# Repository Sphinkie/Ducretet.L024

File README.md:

# Ducretet.L024
 Vintage MP3 player

### Credits

https://www.pistonsoft.com/bpm-detector.html

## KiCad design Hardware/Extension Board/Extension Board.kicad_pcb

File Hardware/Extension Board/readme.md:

# DUCRETET L.024

## Extension Board

### Principe

Cette carte réalise l'adaptation des différents controles avec les Entrées/Sorties de l'Arduino.

### Fonctionnalités

* Adaptation pour les LEDs
* Adaptation pour les lampes
* Adaptation pour la lecture du condensateur variable
* Adaptation pour lecture du Mode
* Adaptation pour lecture du commutateur Next/Again
* Etage alimentation : 6V / 12V

### Connexions

* **CNX MODE** = 4 pins : GND + Mode1 + Mode2 + Mode3
* **CNX OLED** = 4 pins = VCC + GND + SDA + SCL (bus I2C)
* **CNX NEXT_AGAIN** = 3 pins = GND + Next + Again
* **CNX LEDS** = 5x 2 pins = VCC + LED_n
* **TEST POINTS** = Vin + 6V + 12V + GND
* **JMP_TUNE** = 2 jumpers : Use_C1 + Use_C2
* **CNX TUNE** = 3 pins = C0 + C1 + C2

### Etage Alimentation

* **CNX_LAMPS** = 2 pins = 6V + LAMPS
* **CNX6V ** = 2 pins = VCC + GND  = Wire2board vers Arduino
* **CNX 12V** = 2 pins = 12V + GND  = Wire2board vers Ampli
* **CNX POWER_IN** = 2 pins = VIN + GND  = Wire2board
* **CNX ON_OFF** = 2 pins

## Schemas

Le **schema électronique** est accessible ici: [Extension board schematic](Extension%20Board.pdf).

ainsi que  le schéma d'implantation (couche de fabrication) [Extension Board PCB](Gerbers/Extension%20Board-F_Fab.pdf).

et le schéma du PCB [Extension Board PCB](Extension%20Board%20PCB.pdf).

Accès à la [Bill Of Material](https://sphinkie.github.io/Ducretet.L024/BOM-ExtensionBoard.html).

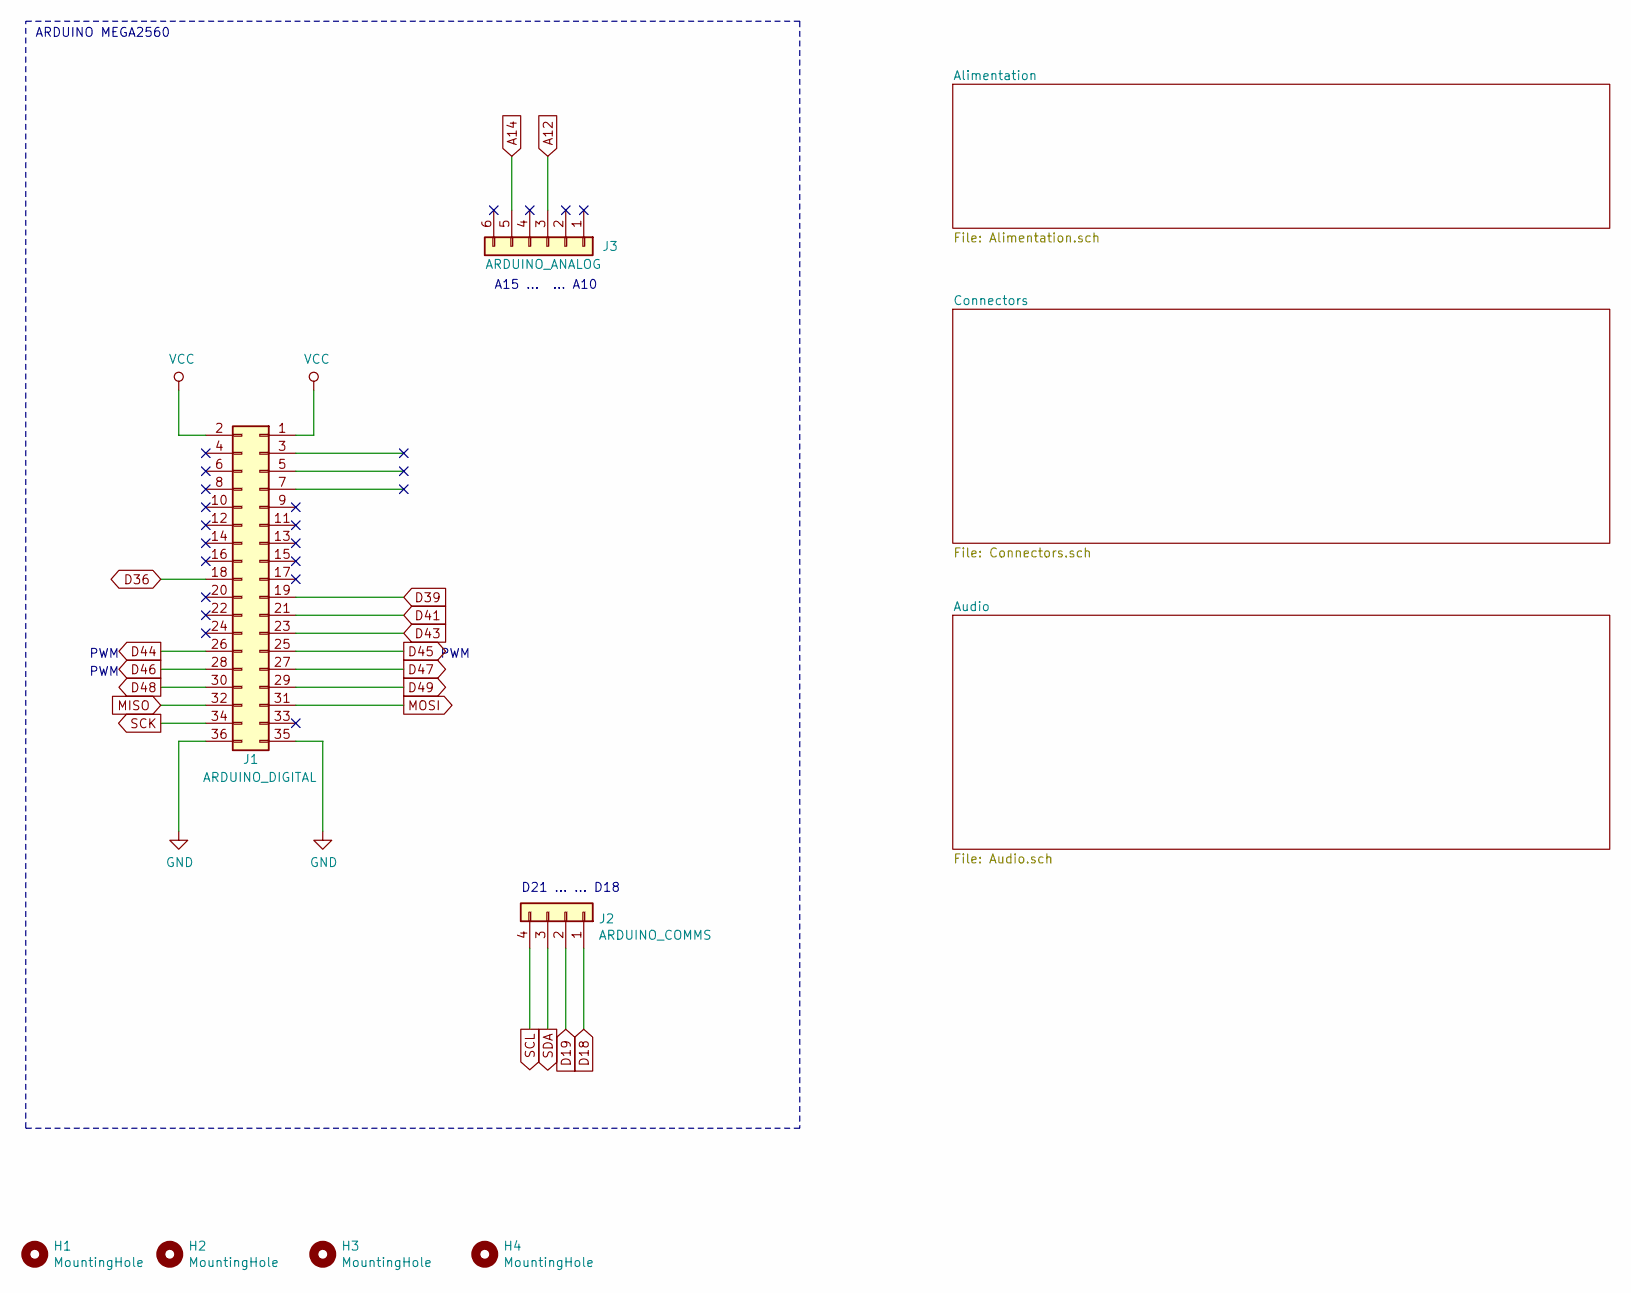
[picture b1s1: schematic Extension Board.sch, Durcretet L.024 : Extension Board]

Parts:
H1, H2, H3, H4: MountingHole; MountingHole_2.7mm_M2.5
J1: ARDUINO_DIGITAL; PinHeader_2x18_P2.54mm_Vertical
J2: ARDUINO_COMMS; PinHeader_1x04_P2.54mm_Vertical
J3: ARDUINO_ANALOG; PinHeader_1x06_P2.54mm_Vertical

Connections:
A12: J3.3; also elsewhere on the board
A14: J3.5; also elsewhere on the board
D18: J2.1; also elsewhere on the board
D19: J2.2; also elsewhere on the board
D36: J1.18; also elsewhere on the board
D39: J1.19; also elsewhere on the board
D41: J1.21; also elsewhere on the board
D43: J1.23; also elsewhere on the board
D44: J1.26; also elsewhere on the board
D45: J1.25; also elsewhere on the board
D46: J1.28; also elsewhere on the board
D47: J1.27; also elsewhere on the board
D48: J1.30; also elsewhere on the board
D49: J1.29; also elsewhere on the board
GND: J1.35, J1.36; also elsewhere on the board
MISO: J1.32; also elsewhere on the board
MOSI: J1.31; also elsewhere on the board
SCK: J1.34; also elsewhere on the board
SCL: J2.4; also elsewhere on the board
SDA: J2.3; also elsewhere on the board
VCC: J1.1, J1.2; also elsewhere on the board

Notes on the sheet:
ARDUINO MEGA2560
A15 ... ... A10
D21 ... ... D18
PWM
PWM

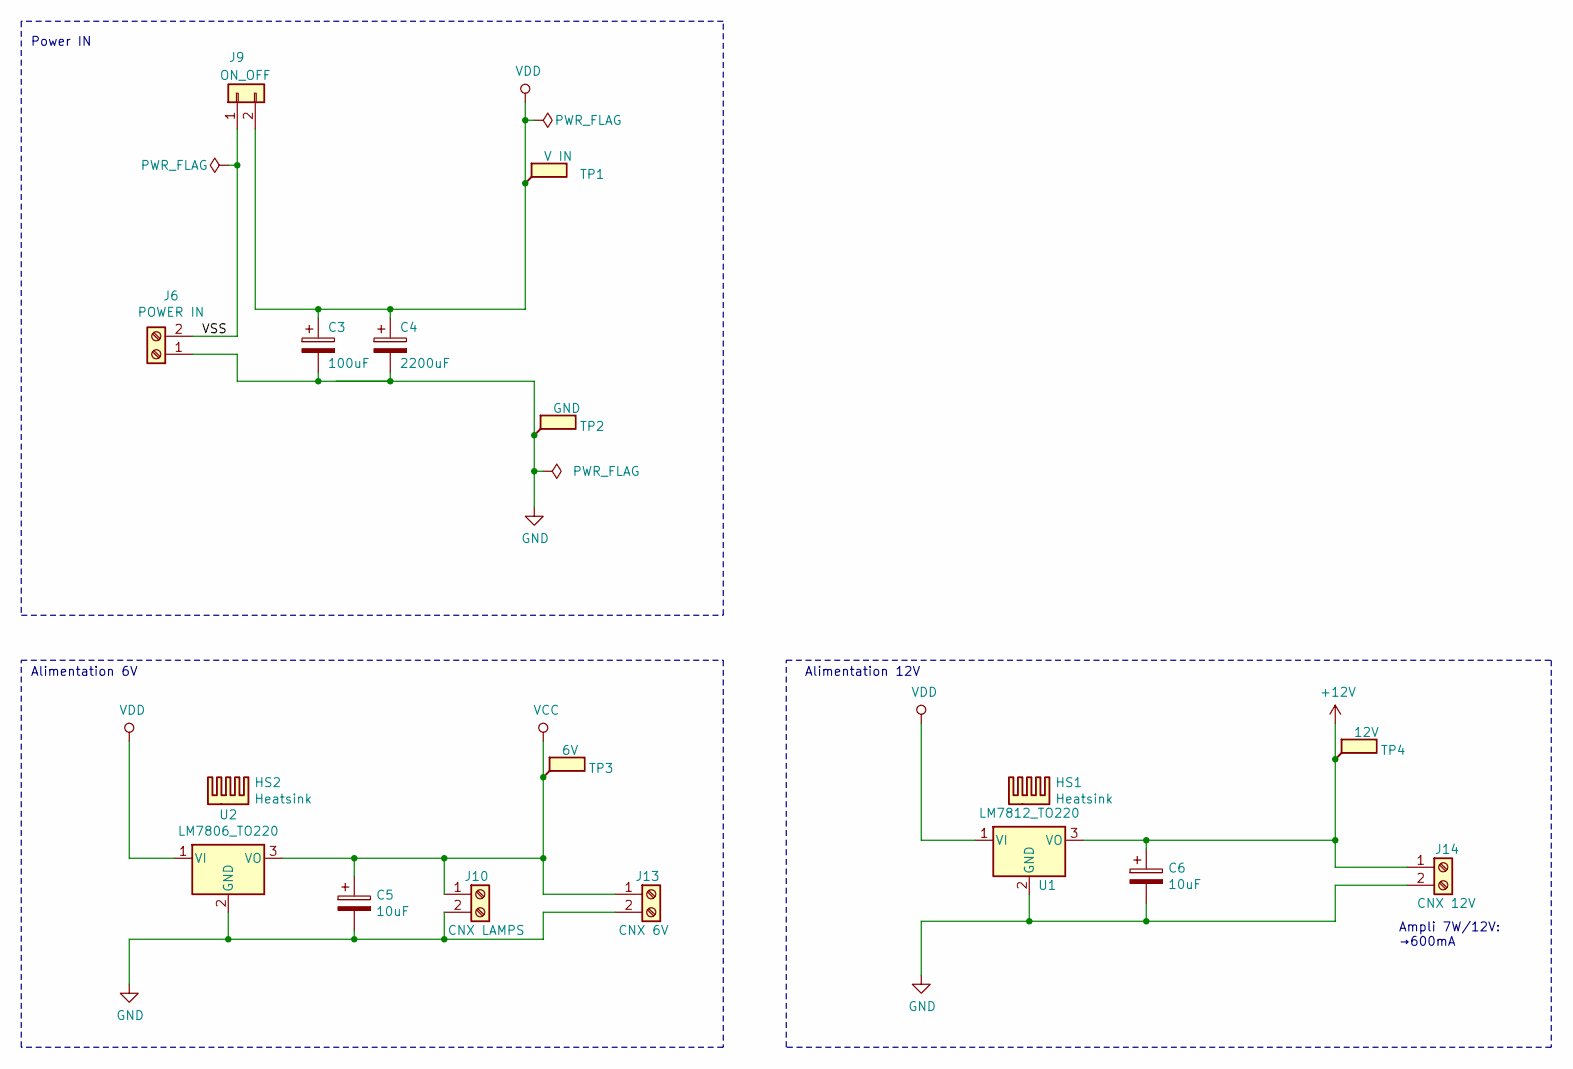
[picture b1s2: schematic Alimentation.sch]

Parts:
C3: 100uF; CP_Axial_L18.0mm_D8.0mm_P25.00mm_Horizontal
C4: 2200uF; CP_Axial_L30.0mm_D18.0mm_P35.00mm_Horizontal
C5, C6: 10uF; CP_Radial_D5.0mm_P2.50mm
HS1, HS2: Heatsink; HeatSink_TO-220
J6: POWER IN; TerminalBlock_Phoenix_MKDS-1,5-2-5.08_1x02_P5.08mm_Horizont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
J9: ON_OFF; JST_XH_B2B-XH-A_1x02_P2.50mm_Vertical
J10: CNX LAMPS; Bloc_de_jonction_CI-MPT_2.54mm_01x02
J13: CNX 6V; TerminalBlock_Phoenix_MKDS-1,5-2-5.08_1x02_P5.08mm_Horizont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
J14: CNX 12V; TerminalBlock_MetzConnect_Type011_RT05502HBWC_1x02_P5.00mm_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
TP1: V IN; TestPoint_Loop_D2.60mm_Drill1.4mm_Beaded
TP2: GND; TestPoint_Loop_D2.60mm_Drill1.4mm_Beaded
TP3: 6V; TestPoint_Loop_D2.60mm_Drill1.4mm_Beaded
TP4: 12V; TestPoint_Loop_D2.60mm_Drill1.4mm_Beaded
U1: LM7812_TO220; TO-220-3_Vertical
U2: LM7806_TO220; TO-220-3_Vertical

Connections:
+12V: C6.1, J14.1, TP4.1, U1.3 (VO)
/Alimentation/VSS: J6.2, J9.1
GND: C3.2, C4.2, C5.2, C6.2, J6.1, J10.2, J13.2, J14.2, TP2.1, U1.2 (GND), U2.2 (GND); also elsewhere on the board
VCC: C5.1, J10.1, J13.1, TP3.1, U2.3 (VO); also elsewhere on the board
VDD: C3.1, C4.1, J9.2, TP1.1, U1.1 (VI), U2.1 (VI)

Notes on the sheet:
Ampli 7W/12V: →600mA
Alimentation 12V
Alimentation 6V
Power IN

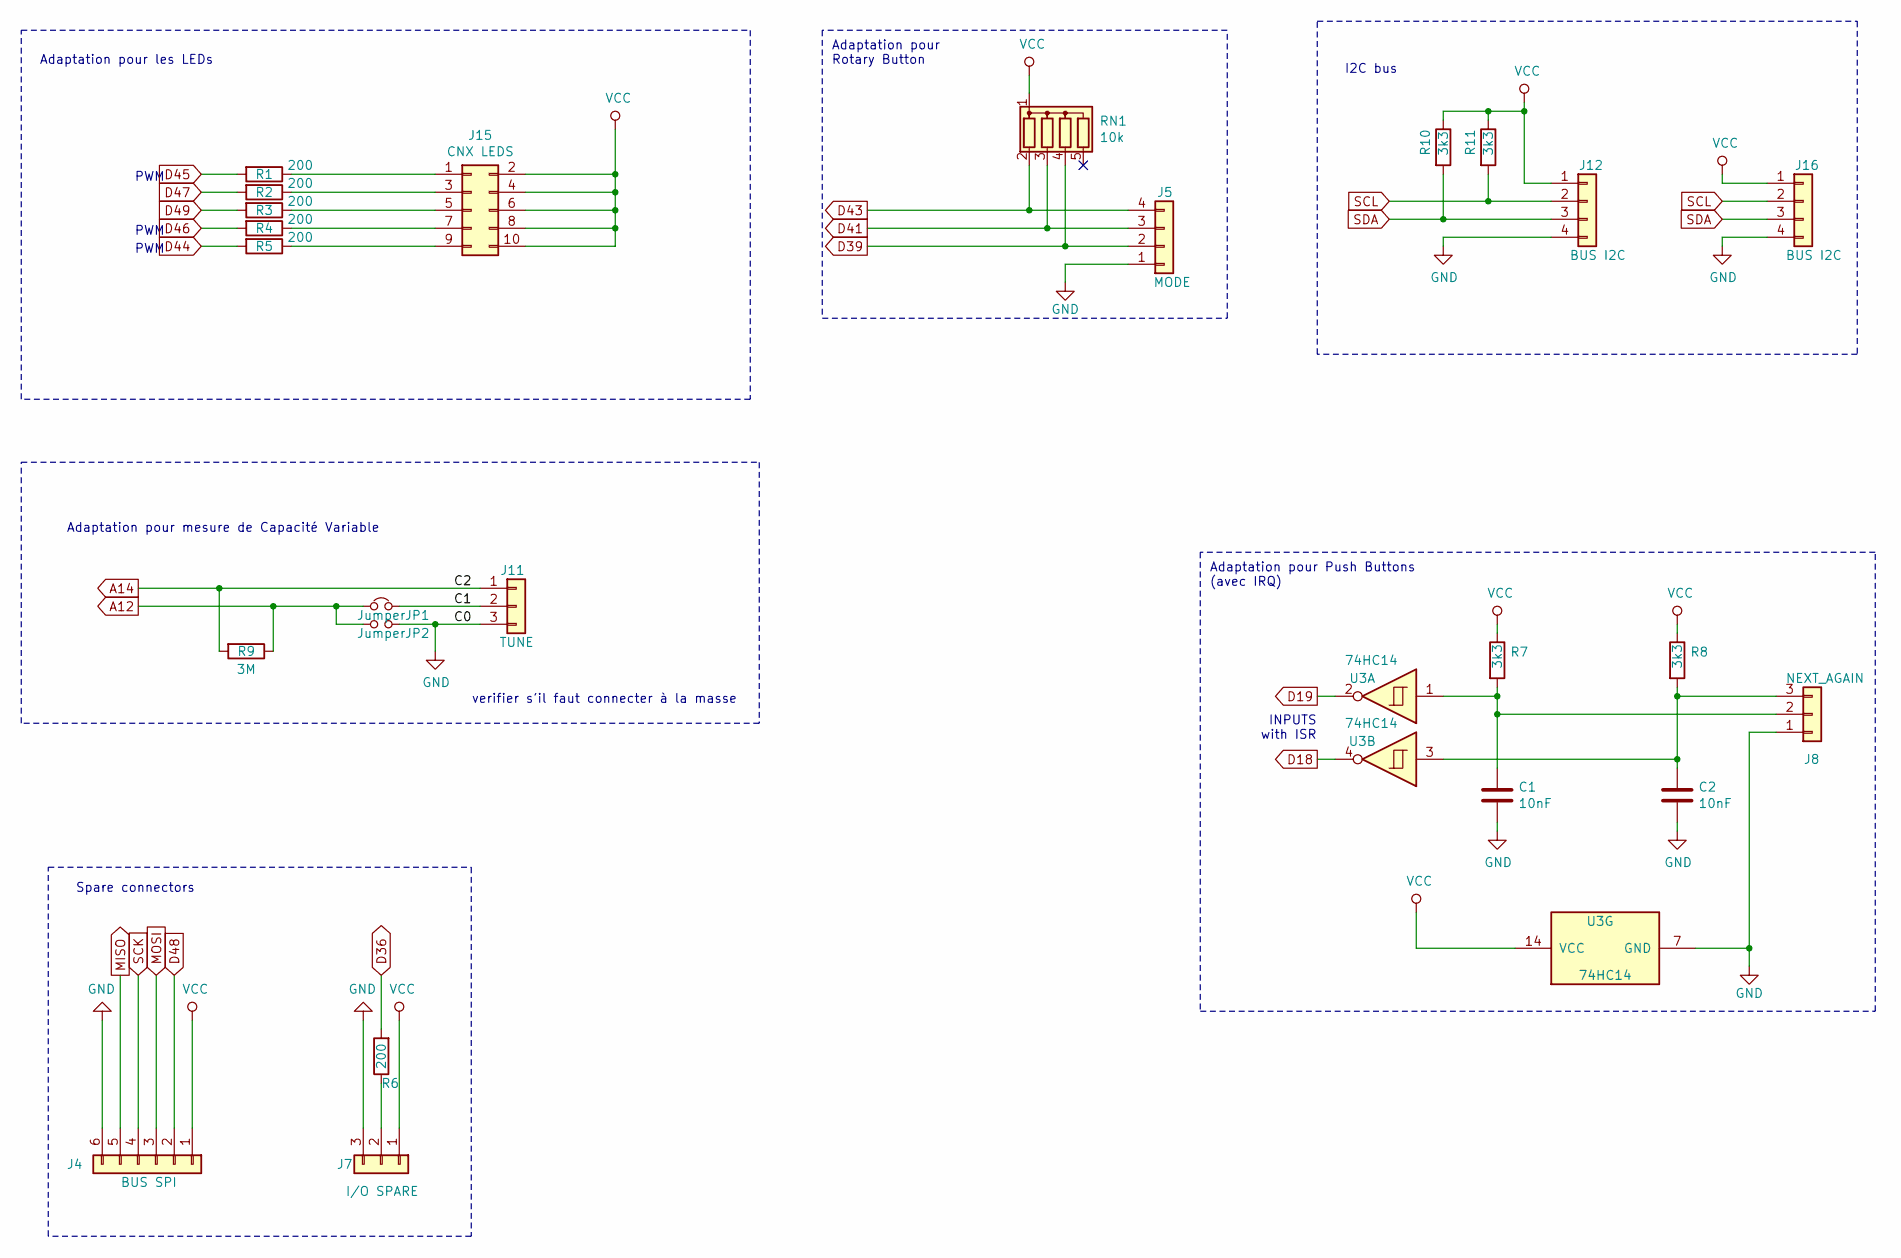
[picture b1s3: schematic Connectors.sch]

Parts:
C1, C2: 10nF; C_Rect_L7.2mm_W2.5mm_P5.00mm_FKS2_FKP2_MKS2_MKP2
J4: BUS SPI; JST_XH_B6B-XH-AM_1x06_P2.50mm_Vertical
J5: MODE; JST_XH_B4B-XH-A_1x04_P2.50mm_Vertical
J7: I/O SPARE; JST_XH_B3B-XH-AM_1x03_P2.50mm_Vertical
J8: NEXT_AGAIN; JST_XH_B3B-XH-A_1x03_P2.50mm_Vertical
J11: TUNE; JST_XH_B3B-XH-A_1x03_P2.50mm_Vertical
J12, J16: BUS I2C; JST_XH_B4B-XH-A_1x04_P2.50mm_Vertical
J15: CNX LEDS; HE10-10P-horizontal
JP1, JP2: Jumper; PinHeader_1x02_P2.54mm_Vertical
R1, R2, R3, R4, R5, R6: 200; R_Axial_DIN0207_L6.3mm_D2.5mm_P10.16mm_Horizontal
R7, R8, R10, R11: 3k3; R_Axial_DIN0207_L6.3mm_D2.5mm_P10.16mm_Horizontal
R9: 3M; R_Axial_DIN0309_L9.0mm_D3.2mm_P15.24mm_Horizontal
RN1: 10k; R_Array_SIP5
U3: 74HC14; DIP-14_W7.62mm_Socket_LongPads

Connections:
/Connectors/C1: J11.2, JP1.2
A12: JP1.1, JP2.1, R9.1; also elsewhere on the board
A14: J11.1, R9.2; also elsewhere on the board
D18: U3.4; also elsewhere on the board
D19: U3.2; also elsewhere on the board
D36: R6.2; also elsewhere on the board
D39: J5.2, RN1.4 (R3); also elsewhere on the board
D41: J5.3, RN1.3 (R2); also elsewhere on the board
D43: J5.4, RN1.2 (R1); also elsewhere on the board
D44: R5.2; also elsewhere on the board
D45: R1.2; also elsewhere on the board
D46: R4.2; also elsewhere on the board
D47: R2.2; also elsewhere on the board
D48: J4.2; also elsewhere on the board
D49: R3.2; also elsewhere on the board
GND: C1.2, C2.2, J4.6, J5.1, J7.3, J8.1, J11.3, J12.4, J16.4, JP2.2, U3.7 (GND); also elsewhere on the board
MISO: J4.5; also elsewhere on the board
MOSI: J4.3; also elsewhere on the board
unnamed: C1.1, J8.2, R7.2, U3.1
unnamed: C2.1, J8.3, R8.2, U3.3
unnamed: J7.2, R6.1
unnamed: J15.1, R1.1
unnamed: J15.3, R2.1
unnamed: J15.5, R3.1
unnamed: J15.7, R4.1
unnamed: J15.9, R5.1
SCK: J4.4; also elsewhere on the board
SCL: J12.2, J16.2, R11.2; also elsewhere on the board
SDA: J12.3, J16.3, R10.2; also elsewhere on the board
VCC: J4.1, J7.1, J12.1, J15.2, J15.4, J15.6, J15.8, J15.10, J16.1, R7.1, R8.1, R10.1, R11.1, RN1.1 (common), U3.14 (VCC); also elsewhere on the board

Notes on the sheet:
Adaptation pour les LEDs
PWM
Spare connectors
Adaptation pour Rotary Button
Adaptation pour Push Buttons (avec IRQ)
INPUTS with ISR
I2C bus
Adaptation pour mesure de Capacité Variable
verifier s'il faut connecter à la masse

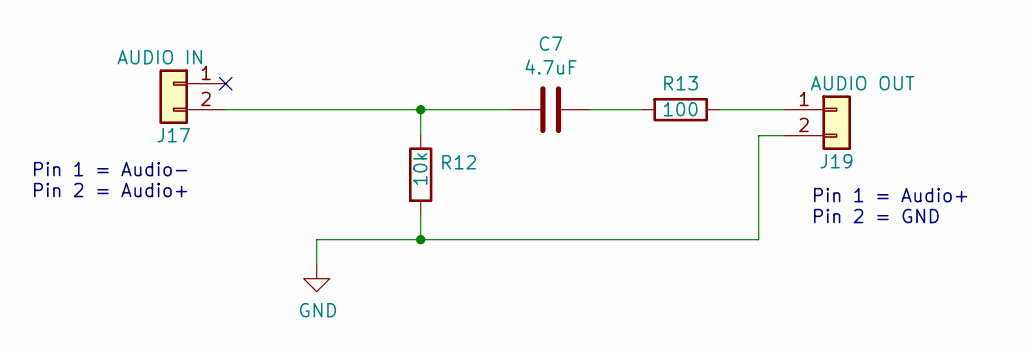
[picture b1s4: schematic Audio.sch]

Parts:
C7: 4.7uF; C_Axial_L17.0mm_D7.0mm_P25.00mm_Horizontal
J17: AUDIO IN; Bloc_de_jonction_CI-MPT_2.54mm_01x02
J19: AUDIO OUT; Bloc_de_jonction_CI-MPT_2.54mm_01x02
R12: 10k; R_Axial_DIN0207_L6.3mm_D2.5mm_P10.16mm_Horizontal
R13: 100; R_Axial_DIN0207_L6.3mm_D2.5mm_P10.16mm_Horizontal

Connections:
GND: J19.2, R12.2; also elsewhere on the board
unnamed: C7.1, J17.2, R12.1
unnamed: C7.2, R13.2
unnamed: J19.1, R13.1

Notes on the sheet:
Pin 1 = Audio- Pin 2 = Audio+
Pin 1 = Audio+ Pin 2 = GND

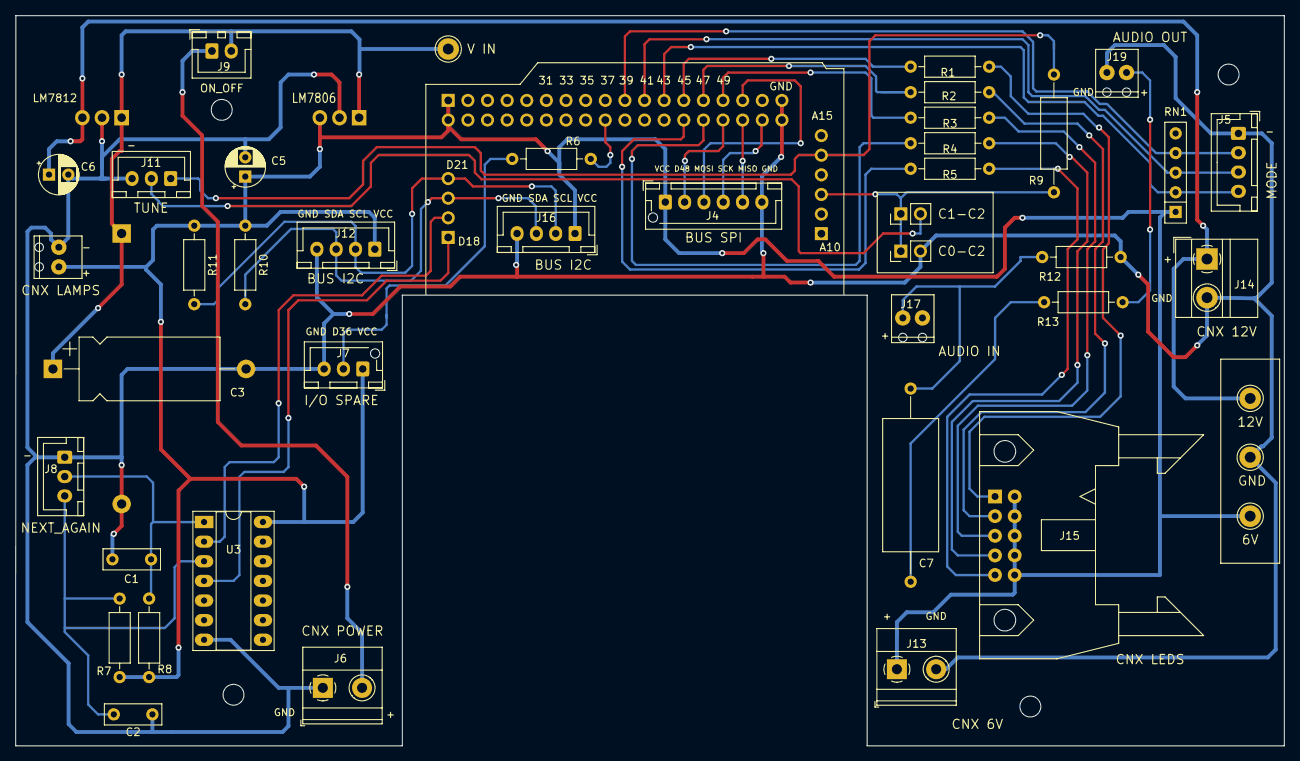
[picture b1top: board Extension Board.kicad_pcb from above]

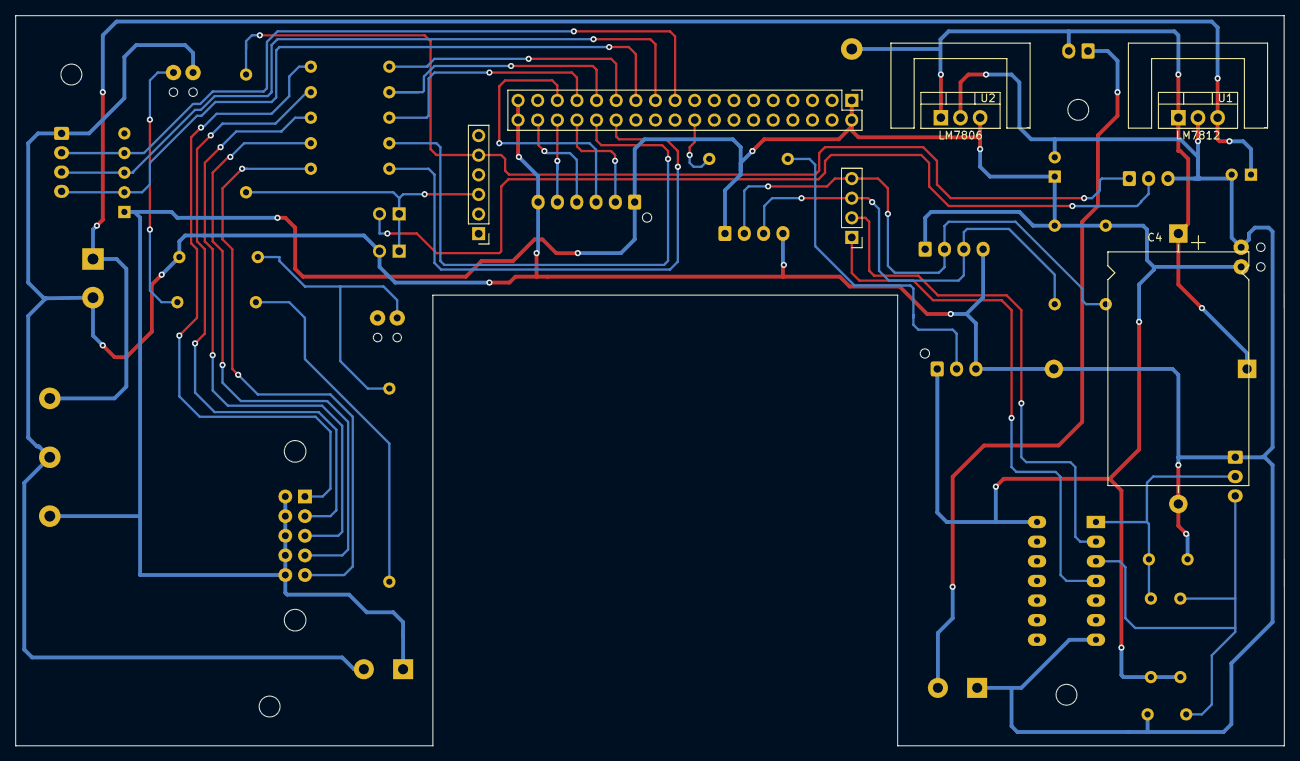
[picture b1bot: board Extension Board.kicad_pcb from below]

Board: 2 copper layers, 164.2 x 94.5 mm, 54 parts (8 on the bottom side), 36 nets.

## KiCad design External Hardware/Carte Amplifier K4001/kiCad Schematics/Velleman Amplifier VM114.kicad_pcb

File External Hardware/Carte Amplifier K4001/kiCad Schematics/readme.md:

# Ducretet L.024

## Amplifier Board : Schematics

Amplificateur audio mono 4W.

Ce répertoire contient le schéma électronique de la carte (au format KiCad).

[Vue du schéma électronique](Velleman%20Amplifier%20VM114.sch)

* Fichier **pro** : fichier **projet** Kicad
* Fichier **sch** : Schéma électronique Kicad
* Fichier **kicad_pcb** : fichier **PCB** Kicad

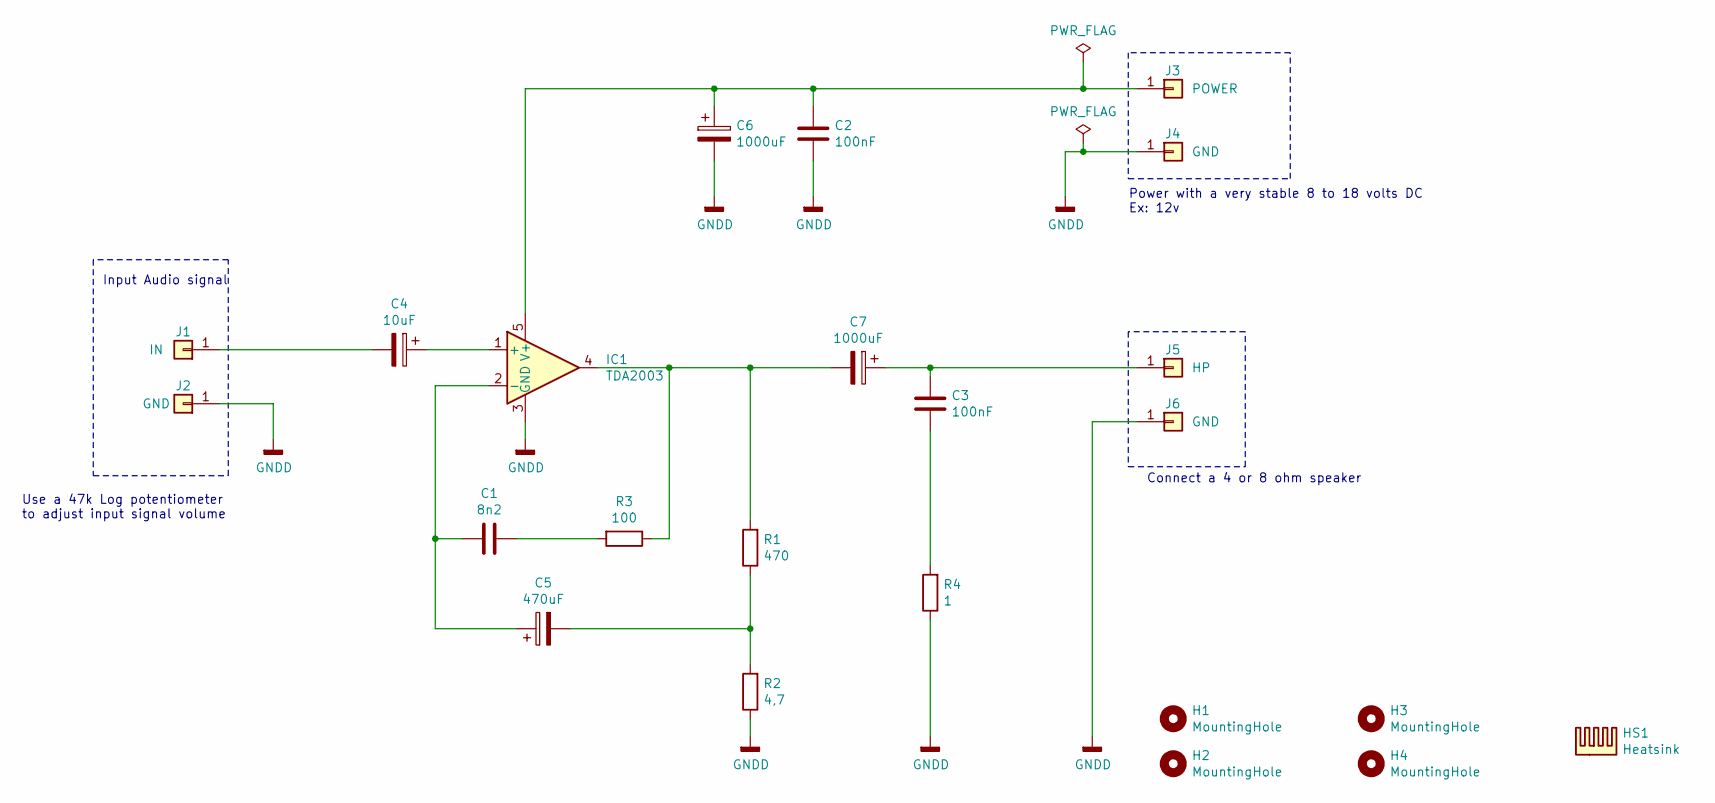
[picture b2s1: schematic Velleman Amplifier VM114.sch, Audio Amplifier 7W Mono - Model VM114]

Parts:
C1: 8n2; C_Disc_D4.3mm_W1.9mm_P5.00mm
C2, C3: 100nF; C_Disc_D4.3mm_W1.9mm_P5.00mm
C4: 10uF; C_Radial_D5.0mm_H11.0mm_P2.00mm
C5: 470uF; C_Radial_D6.3mm_H11.0mm_P2.50mm
C6, C7: 1000uF; C_Radial_D10.0mm_H20.0mm_P5.00mm
H1, H2, H3, H4: MountingHole; MountingHole_3.2mm_M3_DIN965_Pad
HS1: Heatsink; Heatsink_Stonecold_HS-132_32x14mm_2xFixation1.5mm
IC1: TDA2003; TO-220-5_P3.4x3.7mm_StaggerOdd_Lead3.8mm_Vertical
J1: IN; Pin_D1.0mm_L10.0mm
J2, J4, J6: GND; Pin_D1.0mm_L10.0mm
J3: POWER; Pin_D1.0mm_L10.0mm
J5: HP; Pin_D1.0mm_L10.0mm
R1: 470; R_Axial_DIN0204_L3.6mm_D1.6mm_P5.08mm_Horizontal
R2: 4,7; R_Axial_DIN0204_L3.6mm_D1.6mm_P5.08mm_Horizontal
R3: 100; R_Axial_DIN0204_L3.6mm_D1.6mm_P5.08mm_Horizontal
R4: 1; R_Axial_DIN0204_L3.6mm_D1.6mm_P5.08mm_Horizontal

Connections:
GNDD: C2.2, C6.2, IC1.3 (GND), J2.1, J4.1, J6.1, R2.1, R4.1
unnamed: C1.1, R3.2
unnamed: C1.2, C5.1, IC1.2 (-)
unnamed: C2.1, C6.1, IC1.5 (V+), J3.1
unnamed: C3.1, R4.2
unnamed: C3.2, C7.1, J5.1
unnamed: C4.1, IC1.1 (+)
unnamed: C4.2, J1.1
unnamed: C5.2, R1.1, R2.2
unnamed: C7.2, IC1.4, R1.2, R3.1

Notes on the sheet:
Input Audio signal
Connect a 4 or 8 ohm speaker
Power with a very stable 8 to 18 volts DC Ex: 12v
Use a 47k Log potentiometer to adjust input signal volume

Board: 2 copper layers, 23 parts (0 on the bottom side), 10 nets, no tracks yet.

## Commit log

2020-05-19 VERSION 0.1
2020-05-19 version compilable (avec bouchons)
2020-05-20 Ajout de la librarie Adafruit
2020-05-22 Lecture des tags MP3
2020-05-22 On remplace SDFAT.h par SD.h
    Pour ne pas avoir de conflit avec la librairie Adafruit qui utilise SD.h...
2020-05-22 test de 3 méthodes différentes pour récupérer les tags MP3
2020-05-25 Fusion de AddStar et RemoveStar
2020-05-25 Preparation de la carte SD
2020-05-25 Gestion du Field5 : le tag BPM
2020-05-26 Branchement Adafruit
2020-05-27 Reading ID3 tags in MP3 file
2020-05-27 WIP - playing MP3 file
2020-05-28 Fixed. Music is playing.
    Reading MP3 : disabled
2020-05-28 Read IDtags prend un parametre "File"
2020-05-30 v0.3 Mode Random OK.
2020-05-31 Mode YEAR + Mode GENRE
2020-05-31 WIP : Gestion des Beat
2020-05-31 Fix: rewind at ebd of decade.
2020-06-01 Fix: pb de ReadStringUntil() quand on arrive à EOF
    il faut tester: File.available()
2020-06-01 On ne garde le FirstMedia que pour la recherche par YEAR
2020-06-01 Fix: Recherche par YEAR.
2020-06-01 Recherche par BEAT = ok
2020-06-01 Adding ePaper Waveshare library
2020-06-02 Applications de test d'affichage sur ePaper
2020-06-08 ePaper display is replaced by I2C OLED display
2020-06-08 PCB pour Extension board
2020-06-09 PCB Extension board
2020-06-10 PCB Layout complete
2020-06-10 PCB updated.
2020-06-12 Classe Rythlmic opur la gestion du tempo
2020-06-12 gestion Beat
2020-06-15 Sample pictures
2020-06-16 Tests sur OLED display
2020-06-18 Gestion du scrolling pour les polices à taille fixe
2020-06-18 Gestion eds caractères accentués
2020-06-18 Implémentation OLED dans le projet
2020-08-01 update poru Github-Linguist
2020-08-01 update pour Github-Linguist
2022-03-09 Affichage des infos média
2022-03-10 Affichages
2022-03-12 Animation du titre
2022-03-18 Splash Screen
2022-03-20 Carte Ampli Audio
2022-03-20 Audio Amplifier documentation
2022-03-20 OLED Screen update
2022-03-21 Ajout de la documentation doxygen
2022-03-22 update doxyfile documentation
2022-03-31 update shematics
2022-04-03 Ajout FootPrint Library MesModules
2022-04-06 Ajout du connecteur HE10 10P dans la Library KiCad
2022-04-09 Design carte extension
2022-04-11 début du routage
2022-04-13 Routage du PCB
2022-04-13 documentation
2022-04-13 PCB updated
2022-04-13 PCB update (sérigraphie)
2022-04-13 PCB routing completed
2022-04-14 Modèles 3D
2022-04-16 Fichiers Gerber
2022-04-16 Accessoires 3D
2022-04-16 readme
2022-04-17 update FixationPotar
2022-04-19 Fixation du potentiomètre
2022-04-20 Modèle 3D : bouton Volume
2022-04-26 Accessories PLA
2022-04-26 Support Ampli
2022-04-26 update PLA accessories
2022-04-28 documentation update
2022-04-28 documentation access
2022-05-01 update picture
2022-05-02 boitier oled
2022-05-03 3d object
2022-05-14 modélisation 3D
2022-05-15 Fixation potard
2022-05-21 Accessories
2022-05-22 boitier pour douilles E10
2022-05-25 Fixatino pour ampoules E10
2022-05-25 updated docs
2022-05-25 Set theme jekyll-theme-slate
